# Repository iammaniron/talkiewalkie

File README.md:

# TalkieWalkie

A portable 2.4 GHz digital walkie-talkie — designed with KiCad. TalkieWalkie is a compact, battery-powered two-way radio that transmits and receives voice over the 2.4 GHz ISM band using the Nordic nRF24L01 transceiver.

## Features

- **2.4 GHz Wireless Communication** — nRF24L01+ module for digital voice/data transmission
- **Full-Duplex Audio** — Nuvoton NAU8325 audio codec with dual-channel MEMS microphones
- **OLED Display** — 0.91" 128×32 I²C OLED for status, settings, and feedback
- **MicroSD Storage** — Onboard MicroSD slot for audio recording, firmware updates, or configuration
- **RGB LED Indicator** — Multi-color status LED for TX/RX/power indication
- **Battery Powered** — Single 18650 Li-Ion cell for portable operation
- **Compact Board** — 1.6 mm standard thickness, 2-layer PCB

## Hardware

### Bill of Materials

| Reference | Component | Description |
|-----------|-----------|-------------|
| U1 | GLYPH-S3 | Main MCU module (28-pin castellated) |
| U2 | nRF24L01 Breakout | 2.4 GHz RF transceiver module |
| U3 | GMOD-NAU8325 | Audio codec module (Nuvoton NAU8325) |
| U4 | Gsense-2CH-MIC | Dual-channel MEMS microphone module |
| U5 | ER-OLEDM0.91-1x-I2C | 0.91" 128×32 OLED display |
| U6 | GMOD-MICRO SD CARD | MicroSD card slot module |
| BT1 | BK-18650-PC2 | 18650 Li-Ion battery holder |
| D1 | LED_KRGB | RGB LED (common cathode) |
| SW1 | SW_Push | Tactile push button (Omron B3F-315x angled) |
| J1 | Conn_01x05_Pin | 5-pin programming/debug header (1.27 mm pitch) |
| J2,J3 | Conn_01x02_Pin | 2-pin headers (expansion/GPIO) |

### Board Specifications

| Parameter | Value |
|-----------|-------|
| Layers | 2 |
| Thickness | 1.6 mm |
| Min track width | 0.2 mm |
| Min clearance | 0.2 mm |
| Via diameter | 0.6 mm |
| Via drill | 0.3 mm |
| Power rails | +3.3 V, GND |
| Battery | 1× 18650 Li-Ion (3.7 V nominal) |

## Project Status

- [x] Schematic design
- [x] Footprint assignment
- [x] Component placement
- [ ] PCB routing (in progress)
- [ ] Design rule check (DRC)
- [ ] Fabrication & assembly
- [ ] Firmware development

## Repository Structure

```
talkiewalkie/
├── walkietalkie.kicad_pro   # KiCad project file
├── walkietalkie.kicad_sch   # Schematic (top-level sheet)
├── walkietalkie.kicad_pcb   # PCB layout
├── walkietalkie.kicad_prl   # Local project settings
├── README.md                # This file
└── .history/                # Schematic revision history
```

## Tools

- **KiCad** — PCB design (schematic capture + board layout)
- Designed by **PCB CUPID**

## License

Hardware design files are provided as-is for reference and educational purposes.

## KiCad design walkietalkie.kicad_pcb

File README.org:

#+TITLE: teleVox — A DIY Walkie Talkie
#+AUTHOR: ManIron
#+DATE: July 2026

* The Story

It started with a YouTube video.

A friend and fellow creator was building a walkie talkie using Glyph
boards. It worked — technically. But it was held together on a
breadboard, and anyone who has worked with breadboards knows the
struggle: loose connections, noise, wires everywhere, and the constant
question of "why did it just stop working?"

That video planted a seed.

I had been wanting to learn PCB design for a while, and this felt like
the perfect excuse. Instead of designing a full walkie talkie board
from scratch — which would be insane for a first project — I could
design a *carrier board*. A single board that brings the Glyph, the
audio codec, the amplifier, the microphone, the battery management,
and all the supporting circuitry together into one clean package.

It seemed simple enough. A perfect beginner project. A great piece of
content. Maybe a week of work.

I was wrong. And I'm glad I was.

What followed was one of the most intense, frustrating, and rewarding
learning experiences I have ever had. I learned about schematics and
how to read datasheets. I learned about component placement and why
"just connect the pins" is not a routing strategy. I learned about
power distribution, ground planes, decoupling capacitors, and why your
microcontroller resets when the transmitter keys up if you get it
wrong. I learned about buses, differential pairs, ERC and DRC errors,
footprint libraries, design rules, manufacturing constraints, and a
hundred other things I didn't even know existed two weeks earlier.

There were moments when I felt completely stuck. Moments where I
thought I had finished, only to realize I needed to tear something up
and start over. I learned very quickly that a good schematic does not
automatically become a good PCB. The schematic is the vision; the
layout is where reality pushes back.

Thankfully, I was not alone. I had mentors who patiently guided me
through the process. Every time I thought I had figured something out,
they would point out a better way, explain the reasoning behind it,
and push me to think like an engineer, not just a hobbyist following a
tutorial. They reviewed my designs, answered my questions at odd
hours, and made sure I was heading in the right direction.

Today, the board has officially been sent for manufacturing. Seeing
the final design and clicking that "Order" button gave me goosebumps.
Whether it works perfectly on the first try or needs revisions, I have
already learned more than I ever expected.

This is not just a PCB. It is proof that you can start from zero and
build something real.

* What is teleVox?

teleVox is a DIY walkie talkie built around the [[https://www.instagram.com/reezen.xyz/][Glyph]] ecosystem. It is
designed as a carrier board — a custom PCB that integrates off-the-shelf
modules into a single, compact, battery-powered handheld device.

The goal is simple: a walkie talkie that actually works reliably, with
a proper PCB instead of a breadboard, enclosed in a 3D printed shell,
powered by a rechargeable battery.

* How It Works

The system is built around these core blocks:

- *Glyph C3* — the brain. An ESP32-C3 based development board that
  handles the digital audio processing and wireless communication.
- *Audio Codec (ES8388)* — converts analog audio from the microphone
  to digital (ADC) and digital audio back to analog (DAC) for the
  speaker.
- *Microphone* — a MEMS microphone with on-board amplifier for clear
  voice capture.
- *Audio Amplifier (MAX98357)* — a Class-D amplifier that drives the
  speaker with enough volume to be heard clearly.
- *Battery Management* — a TP4056 based charging circuit with
  protection, allowing the device to run on a single 18650 Li-Ion cell
  and charge via USB-C.
- *Power Regulation* — buck and boost converters to provide stable
  3.3V and 5V rails from the battery.
- *User Interface* — physical buttons for PTT (Push-To-Talk), volume,
  and channel selection, plus status LEDs.
- *3D Printed Enclosure* — a custom shell that houses everything in a
  handheld form factor.

* The Design

The PCB was designed in [[https://www.kicad.org/][KiCad]], an open-source EDA tool. The design
went through several iterations:

1. *Schematic Capture* — drawing up the circuit, selecting components,
   checking pinouts against datasheets, and running electrical rules
   checks (ERC).
2. *Component Placement* — arranging everything on the board for
   minimal trace lengths, clean power delivery, and good thermal
   performance.
3. *Routing* — connecting all the nets. This was the hardest part.
   Two-layer board, mixed-signal (audio and digital), careful ground
   plane management, keeping audio traces away from switching noise.
4. *Design Rule Checking (DRC)* — making sure the board meets
   manufacturing constraints: trace width, clearance, via size,
   silkscreen readability.
5. *Gerber Generation* — exporting the manufacturing files and
   sending them off to the fab.

The board is a two-layer design with a solid ground plane on the
bottom layer, star-ground topology for the audio section, and
dedicated power pours for the high-current paths.

* The Enclosure

The teleVox enclosure is a 3D printed shell designed in Fusion 360:

- Two-part clamshell design with screw bosses
- Cutouts for the speaker grille, microphone port, buttons, and USB-C
- Snap-fit battery compartment for easy cell swapping
- Designed for FDM printing with minimal supports

* Repository Structure

- =walkietalkie.kicad_pro= — KiCad project file
- =walkietalkie.kicad_sch= — Schematic
- =walkietalkie.kicad_pcb= — PCB layout
- =walkietalkie.kicad_prl= — Netlist / project locals
- =the final gerber/= — Manufacturing files sent to the fab
- =teleVox.glb= — 3D model of the device
- =teleVox.step= — STEP file for the enclosure / mechanical integration
- =.step= — Additional mechanical data

* Acknowledgments

This project would not have been possible without the people who took
the time to teach, review, and guide. You know who you are — thank you
for making me think like an engineer.

Also huge thanks to the KiCad team for building incredible open-source
tools, and to the ESP32 and audio communities for the libraries and
reference designs that made this possible.

* What's Next?

The boards are at the fab. When they arrive:

- Assembly and soldering
- Bring-up and testing
- Firmware development
- Enclosure printing and fitting
- Field testing

If the first revision has issues — that's okay. That's part of the
process. Each revision will be better than the last.

* License

This project is open-source hardware. Feel free to learn from it,
modify it, and build your own.

#+begin_quote
Built with curiosity, caffeine, and KiCad.
#+end_quote

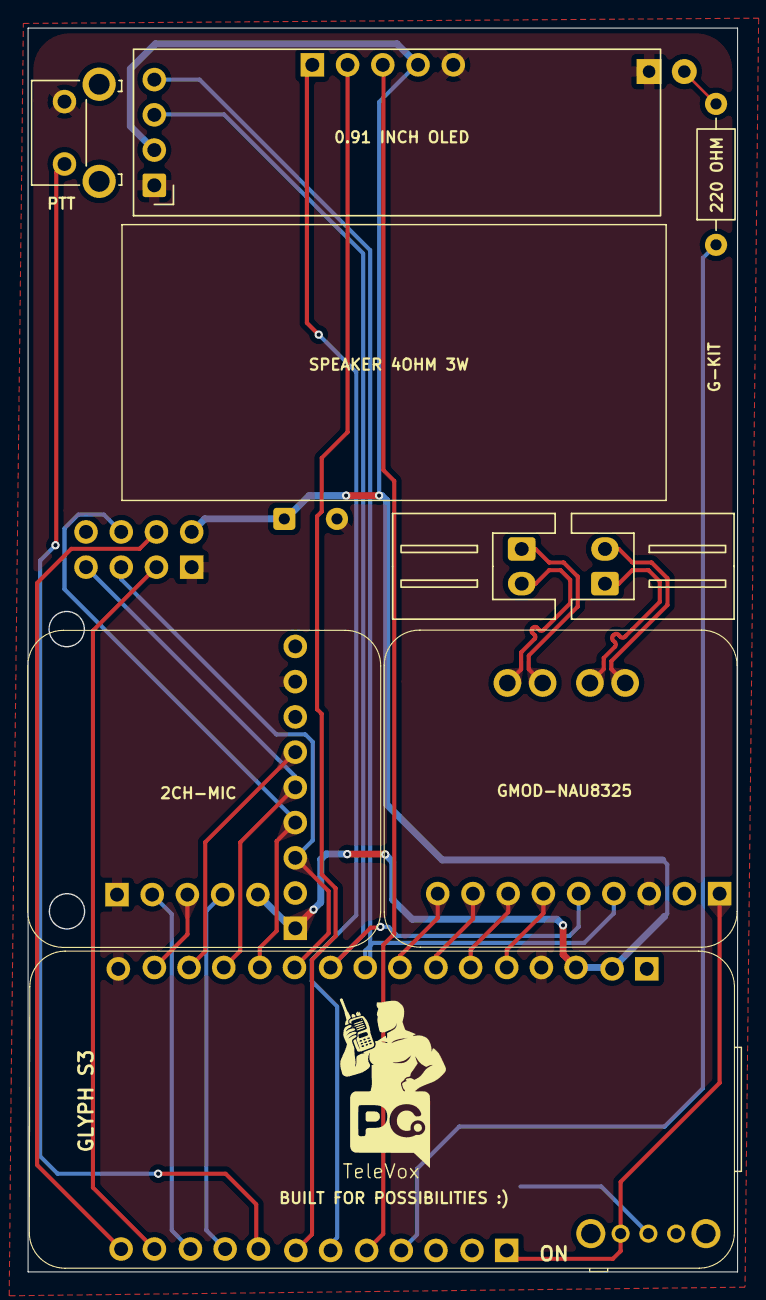
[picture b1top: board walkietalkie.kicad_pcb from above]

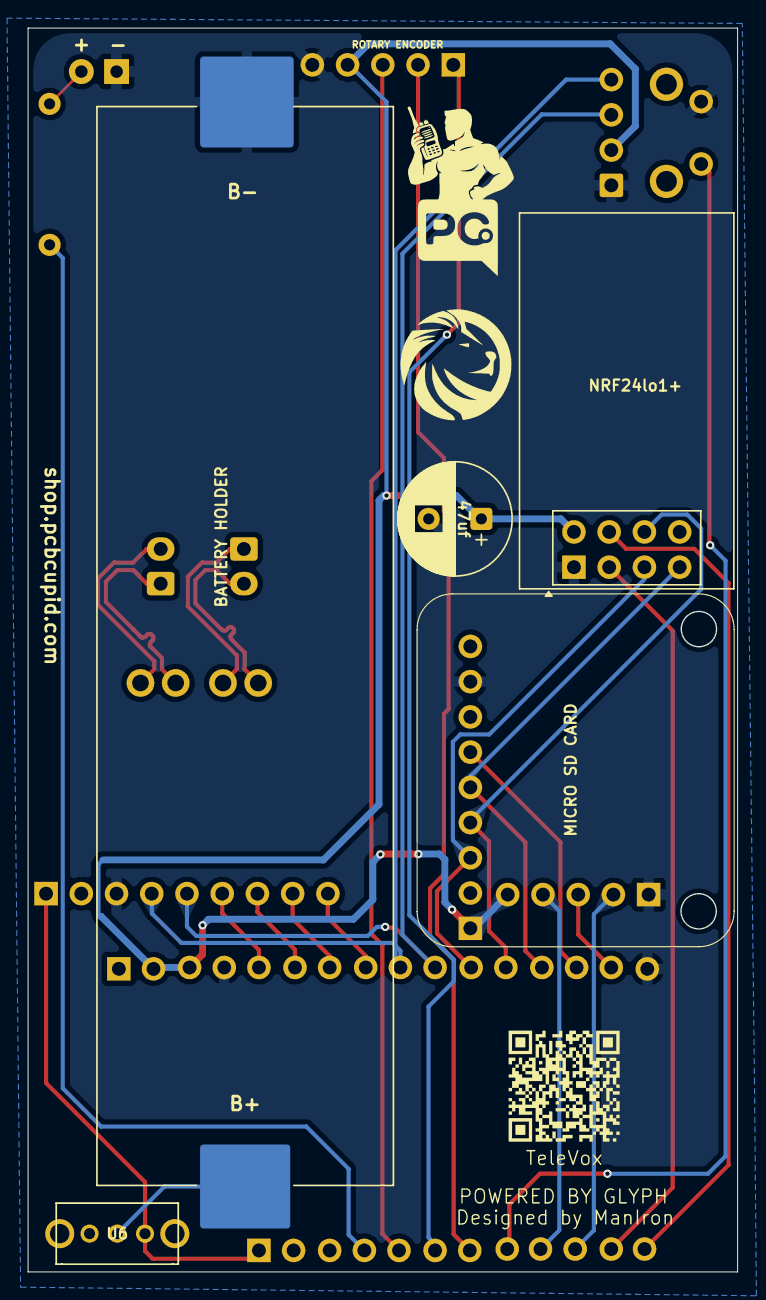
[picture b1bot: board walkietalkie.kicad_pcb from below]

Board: 2 copper layers, 51.2 x 89.7 mm, 15 parts (7 on the bottom side), 29 nets.

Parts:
BT1: BK-18650-PC2; BatteryHolder_1042_1x18650
C1: C_Polarized; CP_Radial_D8.0mm_P3.80mm
D1: LED; LED_D5.0mm
J1: Conn_01x05_Pin; PinHeader_1x05_P2.54mm_Vertical
J2, J3: Conn_01x02_Pin; JST_XH_S2B-XH-A_1x02_P2.50mm_Horizontal
R1: R; R_Axial_DIN0207_L6.3mm_D2.5mm_P10.16mm_Horizontal
SW1: PTT; SW_SPST_Omron_B3F-315x_Angled
U1: glyph-s3
U2: NRF24L01_Breakout; nRF24L01_Breakout
U3: gmod-audio_codec
U4: CH2 mic
U5: gmod-micro_sd
U6: SK12D07VG4
U7: ER_OLEDM0.91_1x-I2C

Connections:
+3V3: C1.1, J1.4, U1.14 (3V3), U1.15 (3V3), U2.2 (VCC), U4.5 (3.3V), U5.1 (3.3V), U7.2 (VCC)
/BAT: U1.12 (BAT), U3.1 (5V), U6.2
/BCLK: U1.18 (D14), U3.7 (BCK)
/CE: U1.2 (SDA), U2.3 (CE)
/CSN: U1.1 (SCL), U2.4 (~CSN)
/ENC_A: J1.1, U1.7 (A8)
/ENC_B: J1.2, U1.6 (A7)
/ENC_SW: J1.3, U1.8 (A9)
/LED: R1.1, U1.9 (A10)
/LRCK: U1.20 (D16), U3.9 (LRCK)
/MI: U1.25 (MI), U2.7 (MISO), U5.5 (MI)
/MIC_SD: U1.27 (TX), U4.3 (SD)
/MO: U1.24 (MO), U2.6 (MOSI), U5.4 (MO)
/MSCK: U1.4 (A2), U4.4 (SCK)
/NAU_DAT: U1.19 (D15), U3.8 (DAT)
/NAU_MCLK: U1.17 (D13), U3.6 (MCLK)
/PTT: SW1.1, U1.5 (A6)
/SCK: U1.23 (SCK), U2.5 (SCK), U5.3 (SCK)
/SCL: U1.22 (D18), U3.5 (SCL), U7.3 (SCL)
/SDA: U1.21 (D17), U3.4 (SDA), U7.4 (SDA)
/WS: U1.3 (A1), U4.2 (WS)
/_LN: J3.1, U3.11 (LN)
/_LP: J3.2, U3.10 (LP)
/_RN: J2.1 (Pin_2), U3.12 (RN)
/_RP: J2.2 (Pin_1), U3.13 (RP)
GND: BT1.2, C1.2, D1.1 (K), J1.5, SW1.2, U1.16 (GND), U1.28 (GND), U2.1 (GND), U3.3 (GND), U4.1 (GND), U5.8 (GND), U7.1 (GND)
unnamed: BT1.1, U6.COM
unnamed: D1.2 (A), R1.2
unnamed: U1.26 (RX), U5.6 (CS)

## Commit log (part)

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2026-06-24 added rough schematics
2026-06-25 schematics done
2026-06-25 schematics is done
2026-06-25 assigning footprints done
2026-06-26 placements of the components are done, routing left
2026-06-26 docs: add project README with BOM and board specs
2026-06-26 docs: add system architecture, signal flow, and how-it-works section
2026-06-30 feat: finalize component placement, routing remaining
2026-06-30 feat: initial routing progress, fix 2ch mic footprint
2026-06-30 feat: routing almost done, GND and VCC remaining
2026-06-30 fix: resolve schematic problems
